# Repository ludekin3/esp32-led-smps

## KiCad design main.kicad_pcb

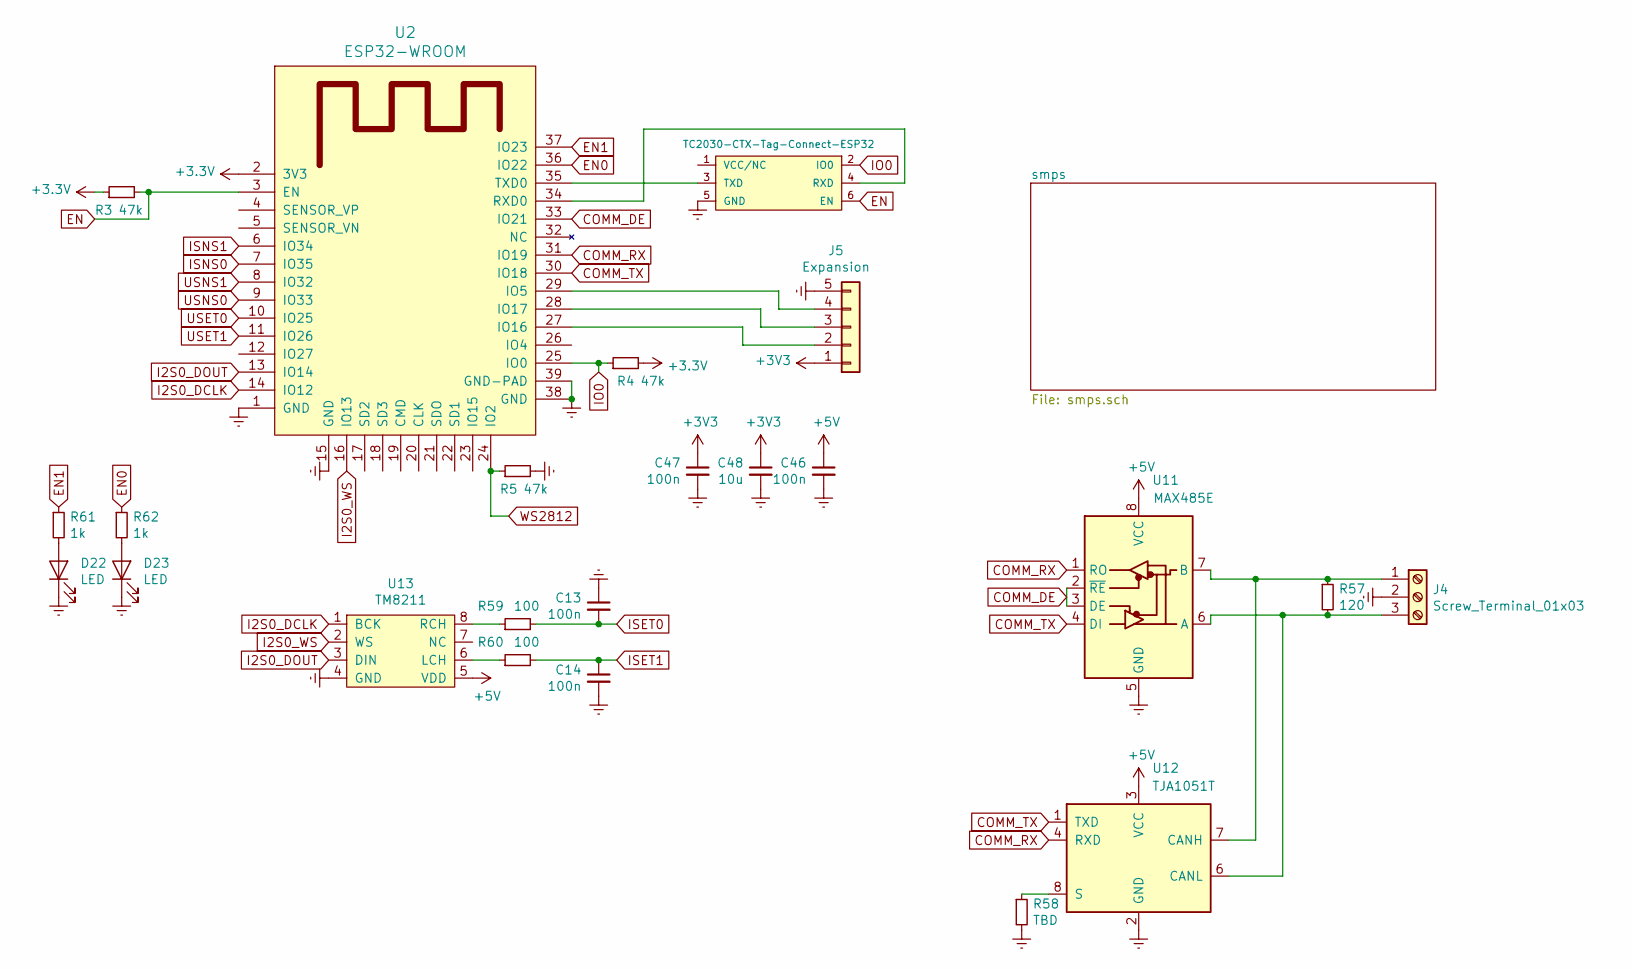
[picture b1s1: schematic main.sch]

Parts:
C13, C14, C46, C47: 100n; C_0603_1608Metric
C48: 10u; C_0603_1608Metric
D22, D23: LED; LED_0603_1608Metric
J4: Screw_Terminal_01x03; TerminalBlock_MetzConnect_Type086_RT03403HBLC_1x03_P3.81mm_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
J5: Expansion; PinSocket_1x05_P2.54mm_Vertical
P1: TC2030-CTX-Tag-Connect-ESP32; TC2030
R3, R4, R5: 47k; R_0603_1608Metric
R57: 120; R_0603_1608Metric
R58: TBD; R_0603_1608Metric
R59, R60: 100; R_0603_1608Metric
R61, R62: 1k; R_0603_1608Metric
U2: ESP32-WROOM; ESP32-WROOM-32
U11: MAX485E; SOIC-8_3.9x4.9mm_P1.27mm
U12: TJA1051T; SOIC-8_3.9x4.9mm_P1.27mm
U13: TM8211; SOIC-8_3.9x4.9mm_P1.27mm

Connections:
+5V: C46.1, U11.8 (VCC), U12.3 (VCC), U13.5 (VDD); also elsewhere on the board
COMM_DE: U2.33 (IO21), U11.2 (~RE), U11.3 (DE)
COMM_RX: U2.31 (IO19), U11.1 (RO), U12.4 (RXD)
COMM_TX: U2.30 (IO18), U11.4 (DI), U12.1 (TXD)
EN: P1.6 (EN), R3.2, U2.3 (EN)
EN0: R62.1, U2.36 (IO22); also elsewhere on the board
EN1: R61.1, U2.37 (IO23); also elsewhere on the board
Earth: C13.1, C14.2, C46.2, C47.2, C48.2, D22.1 (K), D23.1 (K), J4.2, J5.5, P1.5 (GND), R5.2, R58.2, U2.1 (GND), U2.15 (GND), U2.38 (GND), U2.39 (GND-PAD), U11.5 (GND), U12.2 (GND), U13.4 (GND); also elsewhere on the board
I2S0_DCLK: U2.14 (IO12), U13.1 (BCK)
I2S0_DOUT: U2.13 (IO14), U13.3 (DIN)
I2S0_WS: U2.16 (IO13), U13.2 (WS)
IO0: P1.2 (IO0), R4.1, U2.25 (IO0)
ISET0: C13.2, R59.2; also elsewhere on the board
ISET1: C14.1, R60.2; also elsewhere on the board
ISNS0: U2.7 (IO35); also elsewhere on the board
ISNS1: U2.6 (IO34); also elsewhere on the board
unnamed: D22.2 (A), R61.2
unnamed: D23.2 (A), R62.2
unnamed: J4.1, R57.1, U11.7 (B), U12.7 (CANH)
unnamed: J4.3, R57.2, U11.6 (A), U12.6 (CANL)
unnamed: J5.2, U2.27 (IO16)
unnamed: J5.3, U2.28 (IO17)
unnamed: J5.4, U2.29 (IO5)
unnamed: P1.3 (TXD), U2.35 (TXD0)
unnamed: P1.4 (RXD), U2.34 (RXD0)
unnamed: R58.1, U12.8 (S)
unnamed: R59.1, U13.8 (RCH)
unnamed: R60.1, U13.6 (LCH)
USET0: U2.10 (IO25); also elsewhere on the board
USET1: U2.11 (IO26); also elsewhere on the board
USNS0: U2.9 (IO33); also elsewhere on the board
USNS1: U2.8 (IO32); also elsewhere on the board
WS2812: R5.1, U2.24 (IO2)

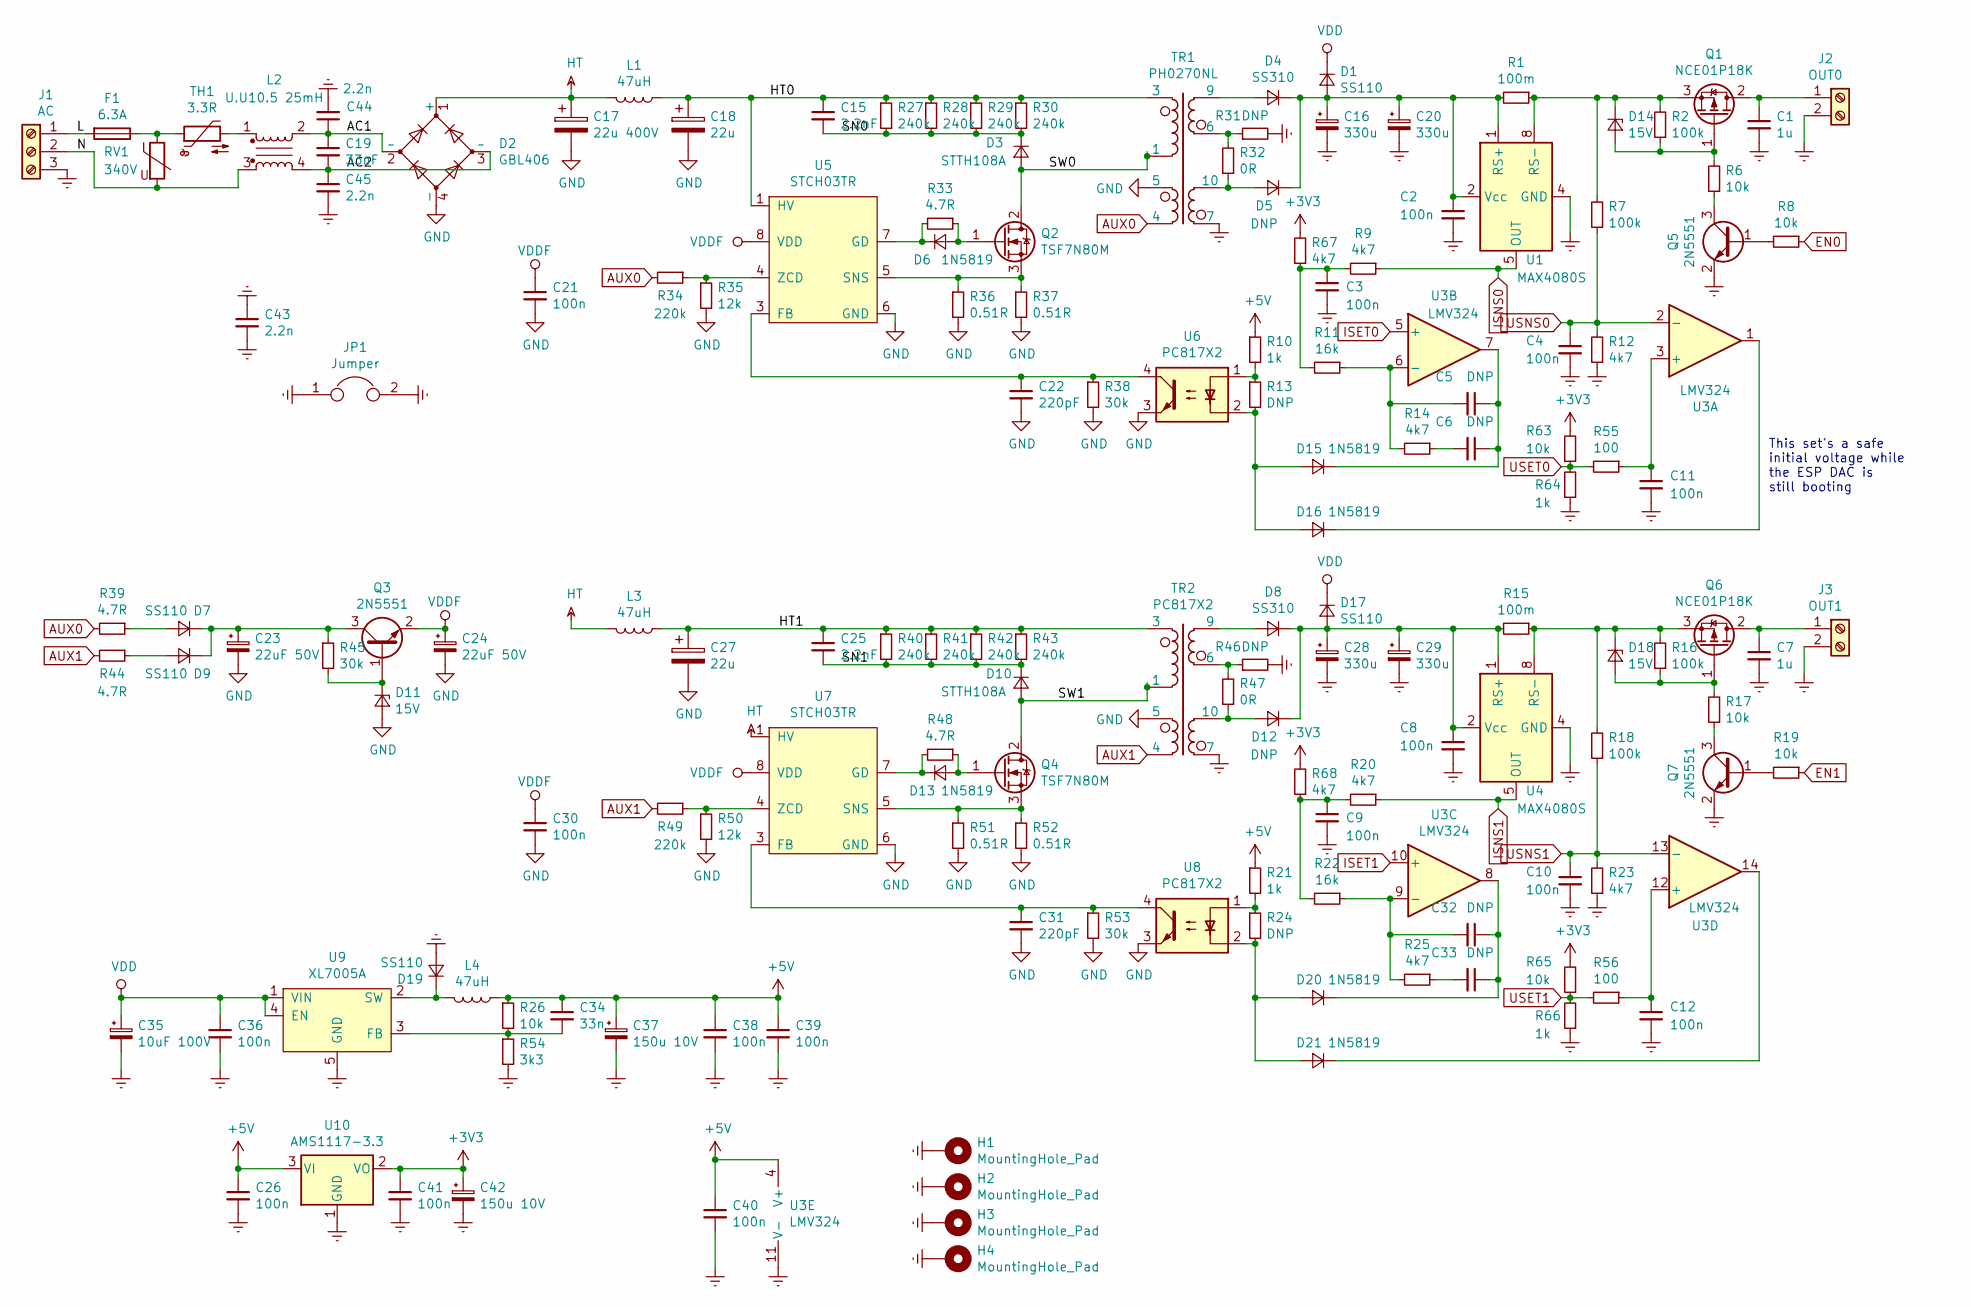
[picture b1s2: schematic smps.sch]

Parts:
C1, C7: 1u; C_Rect_L7.2mm_W5.5mm_P5.00mm_FKS2_FKP2_MKS2_MKP2
C2, C8, C36: 100n; C_0805_2012Metric
C3, C4, C9, C10, C11, C12, C21, C26, C30, C38, C39, C40, C41: 100n; C_0603_1608Metric
C5, C6, C32, C33: DNP; C_0603_1608Metric
C15, C25: 2.2nF; C_1206_3216Metric
C16, C20, C28, C29: 330u; CP_Radial_D16.0mm_P7.50mm
C17: 22u 400V; CP_Radial_D16.0mm_P7.50mm
C18, C27: 22u; CP_Radial_D16.0mm_P7.50mm
C19: 33nF; C_Rect_L16.5mm_W6.0mm_P15.00mm_MKT
C22, C31: 220pF; C_0603_1608Metric
C23, C24: 22uF 50V; CP_Radial_D5.0mm_P2.00mm
C34: 33n; C_0603_1608Metric
C35: 10uF 100V; CP_Radial_D5.0mm_P2.00mm
C37, C42: 150u 10V; CP_Radial_D5.0mm_P2.00mm
C43, C44, C45: 2.2n; RV_Disc_D9mm_W4mm_P5mm
D1, D7, D9, D17, D19: SS110; D_SMA
D2: GBL406; Diode_Bridge_Vishay_GBL
D3, D10: STTH108A; D_SMA
D4, D8: SS310; D_SMA
D5, D12: DNP; D_SMA
D6, D13, D15, D16, D20, D21: 1N5819; D_SOD-123
D11, D14, D18: 15V; D_SOD-123
F1: 6.3A; Fuseholder_TR5_Littelfuse_No560_No460
H1, H2, H3, H4: MountingHole_Pad; MountingHole_3.5mm_Pad_Via
J1: AC; WJ250B-3.5-3P
J2: OUT0; WJ250B-3.5-2P
J3: OUT1; WJ250B-3.5-2P
JP1: Jumper
L1, L3, L4: 47uH; L_Radial_D7.0mm_P3.00mm
L2: U.U10.5 25mH; L_CommonMode_U.U_multi
Q1, Q6: NCE01P18K; TO-252-2
Q2, Q4: TSF7N80M; TO-220-3_Vertical
Q3, Q5, Q7: 2N5551; SOT-23
R1, R15: 100m; R_1206_3216Metric
R2, R7, R16, R18: 100k; R_0603_1608Metric
R6, R8, R17, R19, R26, R63, R65: 10k; R_0603_1608Metric
R9, R12, R14, R20, R23, R25, R67, R68: 4k7; R_0603_1608Metric
R10, R21, R64, R66: 1k; R_0603_1608Metric
R11, R22: 16k; R_0603_1608Metric
R13, R24, R31, R46: DNP; R_0603_1608Metric
R27, R28, R29, R30, R40, R41, R42, R43: 240k; R_1206_3216Metric
R32, R47: 0R; R_0603_1608Metric
R33, R39, R44, R48: 4.7R; R_0603_1608Metric
R34, R49: 220k; R_0603_1608Metric
R35, R50: 12k; R_0603_1608Metric
R36, R37, R51, R52: 0.51R; R_1206_3216Metric
R38, R45, R53: 30k; R_0603_1608Metric
R54: 3k3; R_0603_1608Metric
R55, R56: 100; R_0603_1608Metric
RV1: 340V; RV_Disc_D12mm_W5.1mm_P7.5mm
TH1: 3.3R; RV_Disc_D12mm_W3.9mm_P7.5mm
TR1: PH0270NL; Pulse_PH027NL
TR2: PC817X2; Pulse_PH027NL
U1, U4: MAX4080S; SOIC-8_3.9x4.9mm_P1.27mm
U3: LMV324; SOIC-14_3.9x8.7mm_P1.27mm
U5, U7: STCH03TR; SOIC-8_3.9x4.9mm_P1.27mm
U6, U8: PC817X2; DIP-4_W7.62mm
U9: XL7005A; SOIC-8-1EP_3.9x4.9mm_P1.27mm_EP2.514x3.2mm
U10: AMS1117-3.3; SOT-223-3_TabPin2

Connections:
+5V: C26.1, C34.1, C37.1, C38.1, C39.1, C40.1, L4.1, R10.1, R21.1, R26.1, U3.4 (V+), U10.3 (VI); also elsewhere on the board
/smps/AC1: C19.1, C44.1, D2.2 (~~), L2.2
/smps/AC2: C19.2, C45.1, D2.3 (~~), L2.4
/smps/HT0: C15.1, C18.1, L1.1, R27.1, R28.1, R29.1, R30.1, TR1.3, U5.1 (HV)
/smps/HT1: C25.1, C27.1, L3.1, R40.1, R41.1, R42.1, R43.1, TR2.3
/smps/L: F1.2, J1.1
/smps/N: J1.2, L2.3, RV1.2
/smps/SN0: C15.2, D3.1 (K), R27.2, R28.2, R29.2, R30.2
/smps/SN1: C25.2, D10.1 (K), R40.2, R41.2, R42.2, R43.2
/smps/SW0: D3.2 (A), Q2.2 (D), TR1.1
/smps/SW1: D10.2 (A), Q4.2 (D), TR2.1
AUX0: R34.2, R39.2, TR1.4
AUX1: R44.2, R49.2, TR2.4
EN0: R8.1; also elsewhere on the board
EN1: R19.1; also elsewhere on the board
Earth: C1.2, C2.2, C3.2, C4.2, C7.2, C8.2, C9.2, C10.2, C11.2, C12.2, C16.2, C20.2, C26.2, C28.2, C29.2, C35.2, C36.2, C37.2, C38.2, C39.2, C40.2, C41.2, C42.2, C43.1, C43.2, C44.2, C45.2, D19.2 (A), H1.1, H2.1, H3.1, H4.1, J1.3, J2.2, J3.2, JP1.1, JP1.2, Q5.2 (E), Q7.2 (E), R12.1, R23.1, R31.2, R46.2, R54.2, R64.1, R66.1, TR1.7, TR2.7, U1.4 (GND), U3.11 (V-), U4.4 (GND), U9.5 (GND), U9.6 (GND), U9.7 (GND), U9.8 (GND), U9.9 (GND), U10.1 (GND); also elsewhere on the board
GND: C17.2, C18.2, C21.2, C22.2, C23.2, C24.2, C27.2, C30.2, C31.2, D2.4 (-), D11.2 (A), R35.2, R36.2, R37.2, R38.2, R50.2, R51.2, R52.2, R53.2, TR1.5, TR2.5, U5.6 (GND), U6.3, U7.6 (GND), U8.3
HT: C17.1, D2.1 (+), L1.2, L3.2, U7.1 (HV)
ISET0: U3.5 (+); also elsewhere on the board
ISET1: U3.10 (+); also elsewhere on the board
ISNS0: R9.1, U1.5 (OUT); also elsewhere on the board
ISNS1: R20.1, U4.5 (OUT); also elsewhere on the board
unnamed: C1.1, J2.1, Q1.2 (D)
unnamed: C3.1, R9.2, R11.2, R67.1
unnamed: C5.1, C6.1, D15.1 (K), U3.7
unnamed: C5.2, R11.1, R14.2, U3.6 (-)
unnamed: C6.2, R14.1
unnamed: C7.1, J3.1, Q6.2 (D)
unnamed: C9.1, R20.2, R22.2, R68.1
unnamed: C11.1, R55.1, U3.3 (+)
unnamed: C12.1, R56.1, U3.12 (+)
unnamed: C2.1, C16.1, C20.1, D1.2 (A), D4.1 (K), D5.1 (K), R1.2, U1.1 (RS+), U1.2 (Vcc)
unnamed: C22.1, R38.1, U5.3 (FB), U6.4
unnamed: C23.1, D7.1 (K), D9.1 (K), Q3.3 (C), R45.1
unnamed: C8.1, C28.1, C29.1, D8.1 (K), D12.1 (K), D17.2 (A), R15.2, U4.1 (RS+), U4.2 (Vcc)
unnamed: C31.1, R53.1, U7.3 (FB), U8.4
unnamed: C32.1, C33.1, D20.1 (K), U3.8
unnamed: C32.2, R22.1, R25.2, U3.9 (-)
unnamed: C33.2, R25.1
unnamed: C34.2, R26.2, R54.1, U9.3 (FB)
unnamed: D4.2 (A), TR1.9
unnamed: D5.2 (A), R32.1, TR1.10
unnamed: D6.1 (K), R33.2, U5.7 (GD)
unnamed: D6.2 (A), Q2.1 (G), R33.1
unnamed: D7.2 (A), R39.1
unnamed: D8.2 (A), TR2.9
unnamed: D9.2 (A), R44.1
unnamed: D11.1 (K), Q3.1 (B), R45.2
unnamed: D12.2 (A), R47.1, TR2.10
unnamed: D13.1 (K), R48.2, U7.7 (GD)
unnamed: D13.2 (A), Q4.1 (G), R48.1
unnamed: D14.1 (K), Q1.3 (S), R1.1, R2.2, R7.2, U1.8 (RS-)
unnamed: D14.2 (A), Q1.1 (G), R2.1, R6.2
unnamed: D15.2 (A), D16.2 (A), R13.2, U6.2
unnamed: D16.1 (K), U3.1
unnamed: D18.1 (K), Q6.3 (S), R15.1, R16.2, R18.2, U4.8 (RS-)
unnamed: D18.2 (A), Q6.1 (G), R16.1, R17.2
unnamed: D19.1 (K), L4.2, U9.2 (SW)
unnamed: D20.2 (A), D21.2 (A), R24.2, U8.2
unnamed: D21.1 (K), U3.14
unnamed: F1.1, RV1.1, TH1.1
unnamed: L2.1, TH1.2
unnamed: Q2.3 (S), R36.1, R37.1, U5.5 (SNS)
unnamed: Q4.3 (S), R51.1, R52.1, U7.5 (SNS)
unnamed: Q5.1 (B), R8.2
unnamed: Q5.3 (C), R6.1
unnamed: Q7.1 (B), R19.2
unnamed: Q7.3 (C), R17.1
unnamed: R10.2, R13.1, U6.1
unnamed: R21.2, R24.1, U8.1
unnamed: R31.1, R32.2, TR1.6
unnamed: R34.1, R35.1, U5.4 (ZCD)
unnamed: R46.1, R47.2, TR2.6
unnamed: R49.1, R50.1, U7.4 (ZCD)
USET0: R55.2, R63.1, R64.2; also elsewhere on the board
USET1: R56.2, R65.1, R66.2; also elsewhere on the board
USNS0: C4.1, R7.1, R12.2, U3.2 (-); also elsewhere on the board
USNS1: C10.1, R18.1, R23.2, U3.13 (-); also elsewhere on the board
VDD: C35.1, C36.1, D1.1 (K), D17.1 (K), U9.1 (VIN), U9.4 (EN)
VDDF: C21.1, C24.1, C30.1, Q3.2 (E), U5.8 (VDD), U7.8 (VDD)

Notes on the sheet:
This set's a safe initial voltage while the ESP DAC is still booting

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
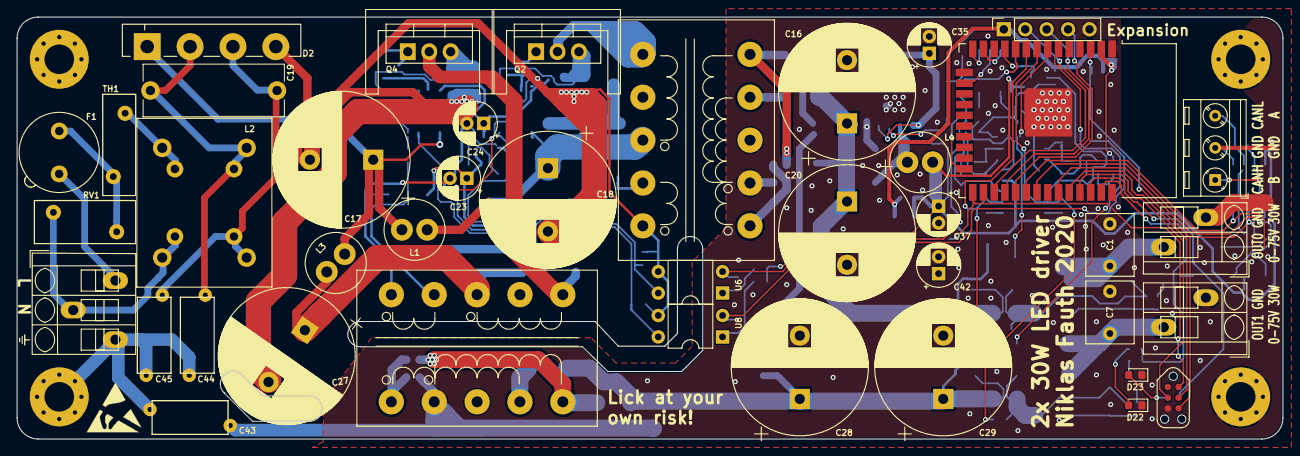
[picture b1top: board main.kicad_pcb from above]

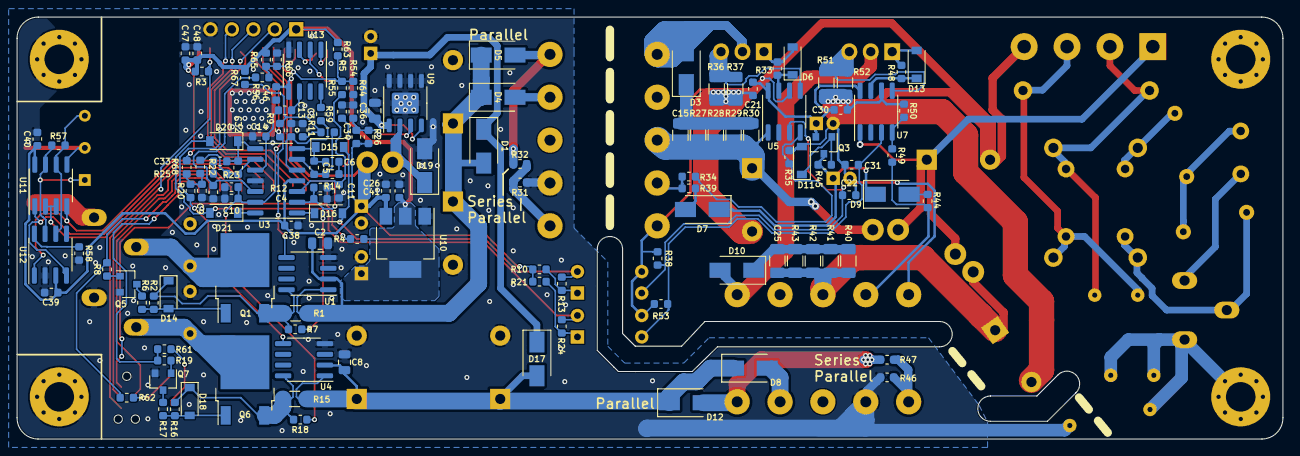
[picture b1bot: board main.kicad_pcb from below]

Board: 2 copper layers, 150.0 x 50.0 mm, 178 parts (133 on the bottom side), 102 nets.

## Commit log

2020-05-06 Update fp-info-cache
2020-05-06 Update smps.sch-bak
2020-05-06 Update main.kicad_pcb-bak
